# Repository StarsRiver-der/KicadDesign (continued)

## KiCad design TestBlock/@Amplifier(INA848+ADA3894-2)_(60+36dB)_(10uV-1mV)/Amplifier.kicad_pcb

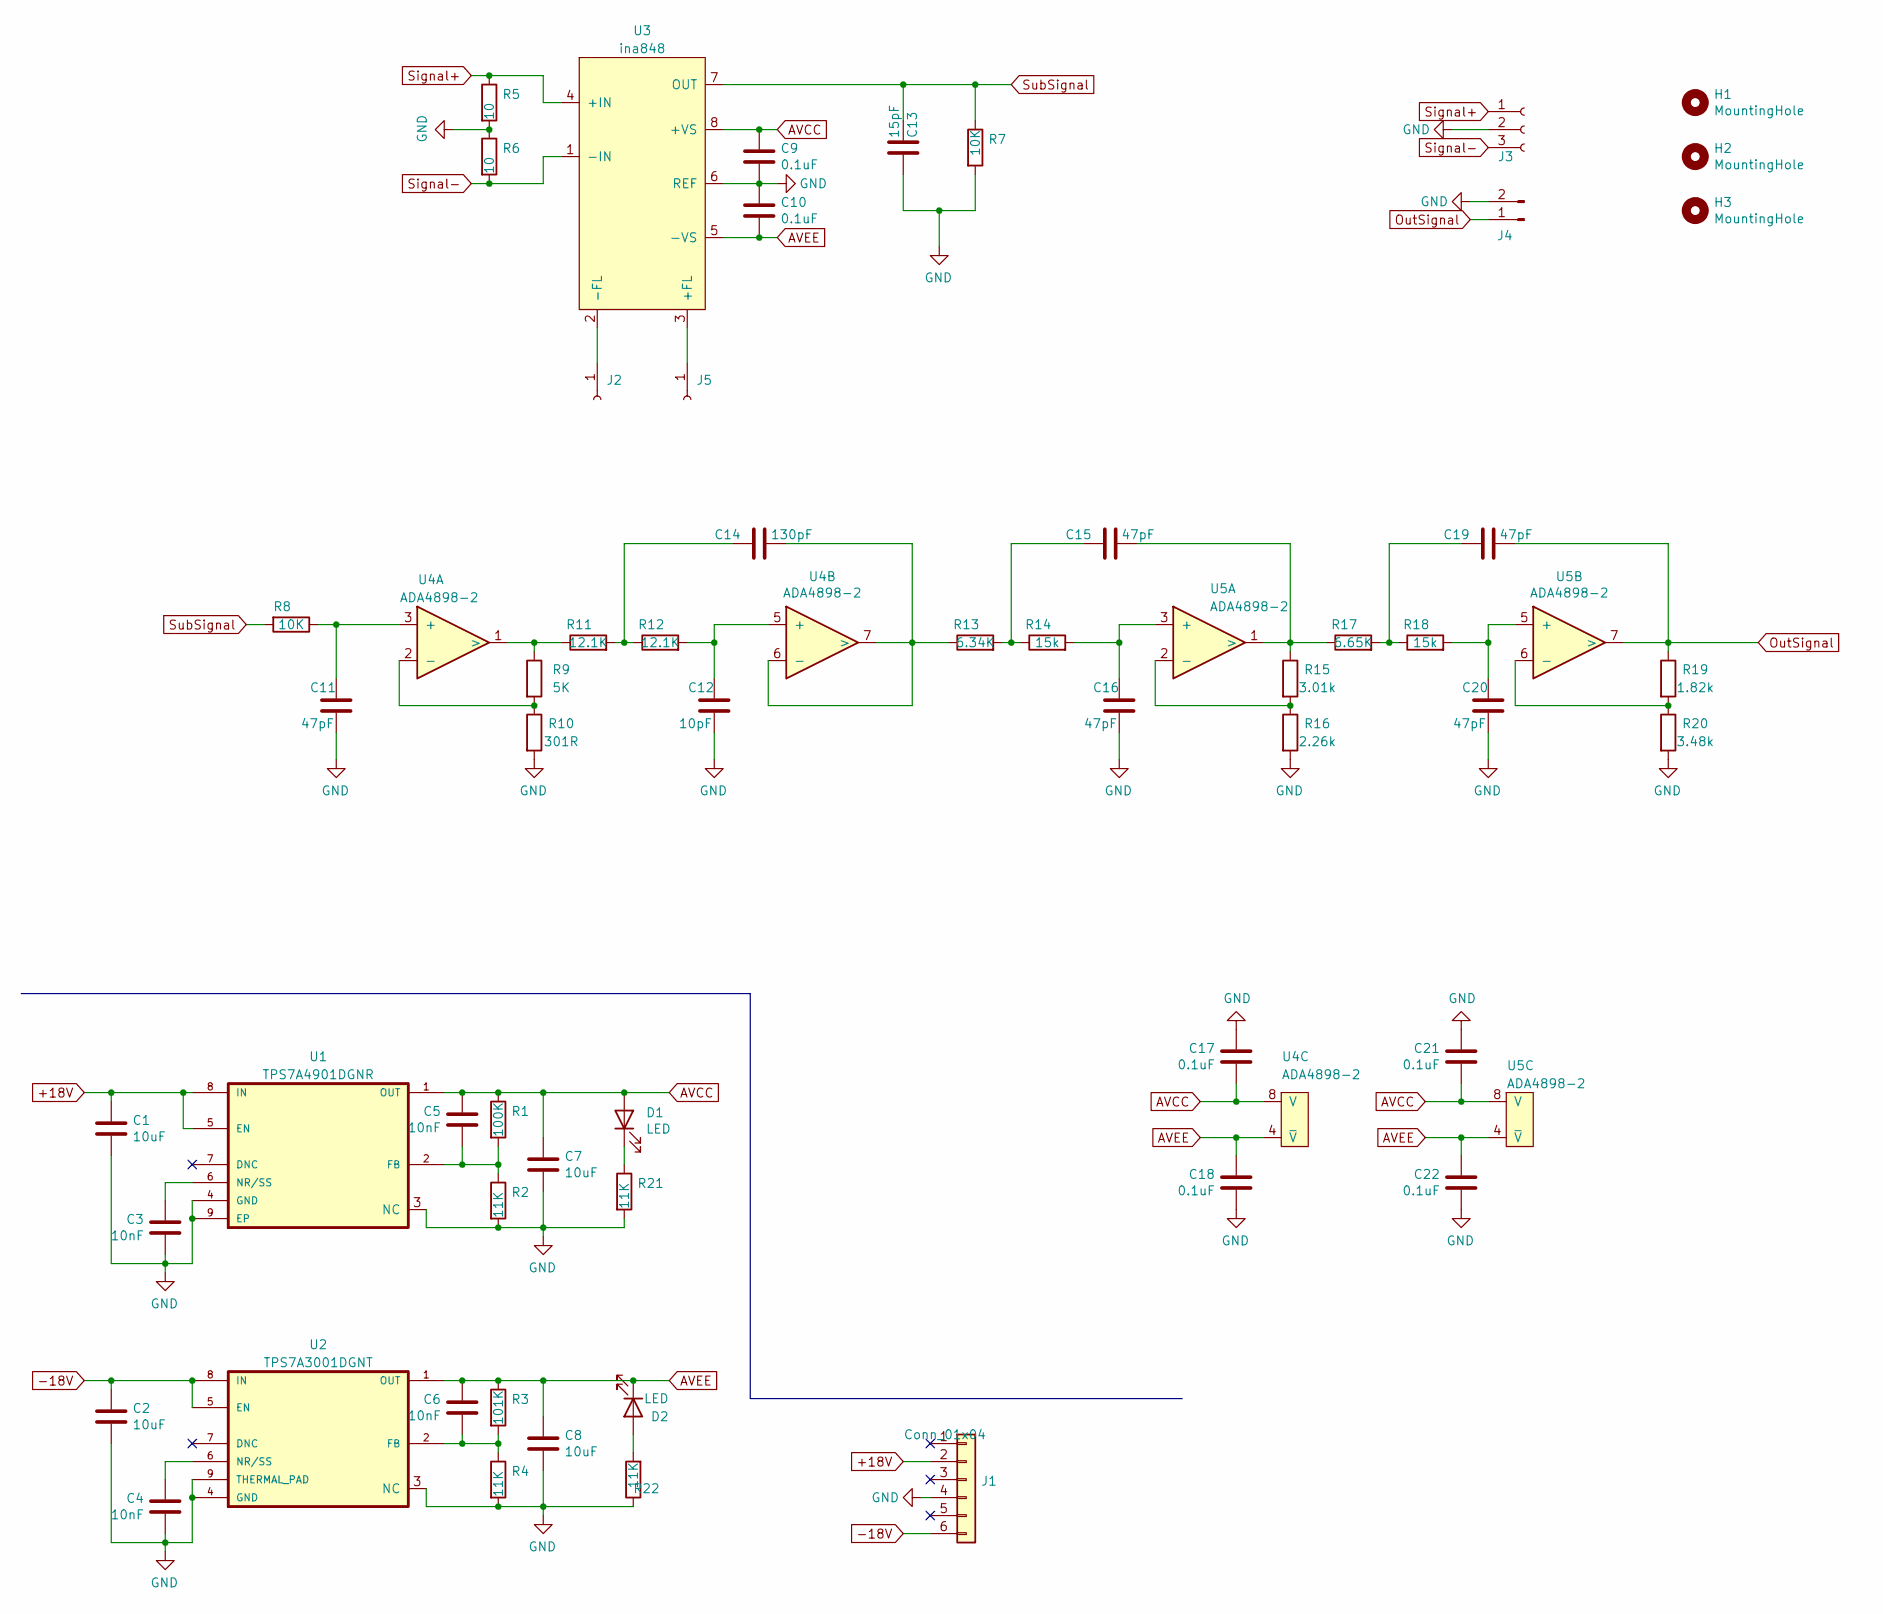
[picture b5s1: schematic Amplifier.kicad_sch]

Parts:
C1, C2, C7, C8: 10uF; C_0603_1608Metric
C3, C4, C5, C6: 10nF; C_0402_1005Metric
C9, C10, C17, C18, C21, C22: 0.1uF; C_1206_3216Metric
C11, C15, C16, C19, C20: 47pF; C_0402_1005Metric
C12: 10pF; C_0402_1005Metric
C13: 15pF; C_0402_1005Metric
C14: 130pF; C_0402_1005Metric
D1, D2: LED; LED_0402_1005Metric
H1, H2, H3: MountingHole; MountingHole_2.2mm_M2
J1: Conn_01x04; Multicomp_MC9A12-1034_2x03_P2.54mm_Vertical
J2, J5: Conn_01x01_Female; MountingPad_1mm
J3: Conn_01x03_Female; PinSocket_1x03_P2.54mm_Vertical
J4: Conn_01x02_Male; SMA_Amphenol_132134_Vertical
R1: 100K; R_0402_1005Metric
R2, R4, R21, R22: 11K; R_0402_1005Metric
R3: 101K; R_0402_1005Metric
R5, R6: 10; R_0402_1005Metric
R7, R8: 10K; R_0402_1005Metric
R9: 5K; R_0402_1005Metric
R10: 301R; R_0402_1005Metric
R11, R12: 12.1K; R_0402_1005Metric
R13: 6.34K; R_0402_1005Metric
R14, R18: 15k; R_0402_1005Metric
R15: 3.01k; R_0402_1005Metric
R16: 2.26k; R_0402_1005Metric
R17: 6.65K; R_0402_1005Metric
R19: 1.82k; R_0402_1005Metric
R20: 3.48k; R_0402_1005Metric
U1: TPS7A4901DGNR; SOP65P490X110-9N
U2: TPS7A3001DGNT; SOP65P490X110-9N
U3: ina848; SOIC-8_3.9x4.9mm_P1.27mm
U4, U5: ADA4898-2; SOIC-8-1EP_3.9x4.9mm_P1.27mm_EP2.29x3mm

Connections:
+18V: C1.1, J1.2, U1.5 (EN), U1.8 (IN)
-18V: C2.1, J1.6, U2.5 (EN), U2.8 (IN)
AVCC: C5.1, C7.1, C9.1, C17.2, C21.2, D1.2 (A), R1.1, U1.1 (OUT), U3.8 (+VS), U4.8 (V), U5.8 (V)
AVEE: C6.1, C8.1, C10.2, C18.1, C22.1, D2.1 (K), R3.1, U2.1 (OUT), U3.5 (-VS), U4.4 (~V), U5.4 (~V)
GND: C1.2, C2.2, C3.2, C4.2, C7.2, C8.2, C9.2, C10.1, C11.2, C12.2, C13.2, C16.2, C17.1, C18.2, C20.2, C21.1, C22.2, J1.4, J3.2, J4.2, R2.2, R4.2, R5.2, R6.1, R7.2, R10.2, R16.2, R20.2, R21.2, R22.1, U1.3 (NC), U1.4 (GND), U1.9 (EP), U2.3 (NC), U2.4 (GND), U2.9 (THERMAL_PAD), U3.6 (REF)
unnamed: C3.1, U1.6 (NR/SS)
unnamed: C4.1, U2.6 (NR/SS)
unnamed: C5.2, R1.2, R2.1, U1.2 (FB)
unnamed: C6.2, R3.2, R4.1, U2.2 (FB)
unnamed: C11.1, R8.1, U4.3 (+)
unnamed: C12.1, R12.2, U4.5 (+)
unnamed: C14.1, R11.2, R12.1
unnamed: C14.2, R13.1, U4.6 (-), U4.7 (>)
unnamed: C15.1, R13.2, R14.1
unnamed: C15.2, R15.1, R17.1, U5.1 (>)
unnamed: C16.1, R14.2, U5.3 (+)
unnamed: C19.1, R17.2, R18.1
unnamed: C20.1, R18.2, U5.5 (+)
unnamed: D1.1 (K), R21.1
unnamed: D2.2 (A), R22.2
unnamed: J2.1, U3.2 (-FL)
unnamed: J5.1, U3.3 (+FL)
unnamed: R9.2, R10.1, U4.2 (-)
unnamed: R9.1, R11.1, U4.1 (>)
unnamed: R15.2, R16.1, U5.2 (-)
unnamed: R19.2, R20.1, U5.6 (-)
OutSignal: C19.2, J4.1, R19.1, U5.7 (>)
Signal+: J3.1, R5.1, U3.4 (+IN)
Signal-: J3.3, R6.2, U3.1 (-IN)
SubSignal: C13.1, R7.1, R8.2, U3.7 (OUT)

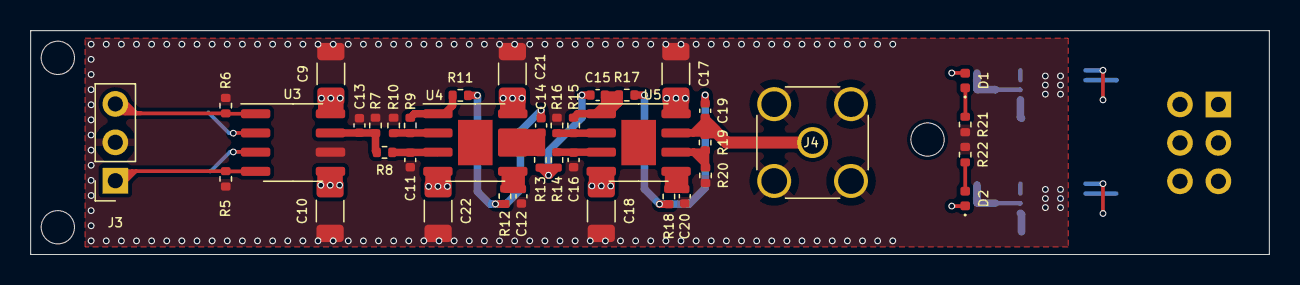
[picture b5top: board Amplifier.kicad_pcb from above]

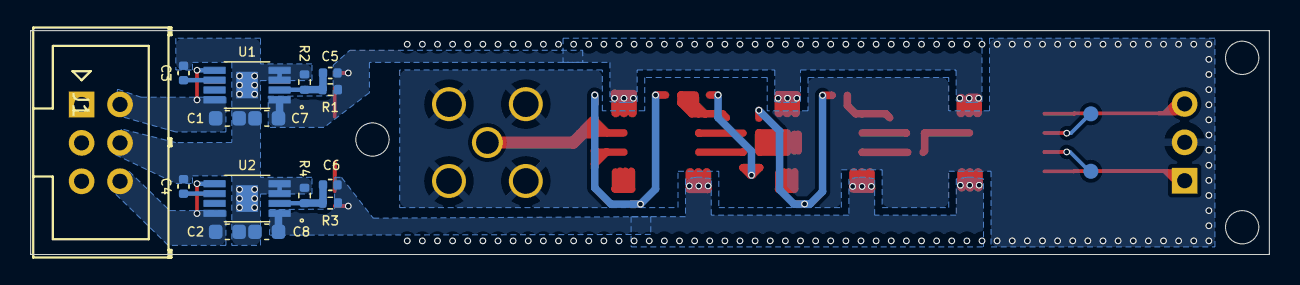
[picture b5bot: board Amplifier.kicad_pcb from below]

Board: 4 copper layers, 81.9 x 14.8 mm, 59 parts (17 on the bottom side), 30 nets.

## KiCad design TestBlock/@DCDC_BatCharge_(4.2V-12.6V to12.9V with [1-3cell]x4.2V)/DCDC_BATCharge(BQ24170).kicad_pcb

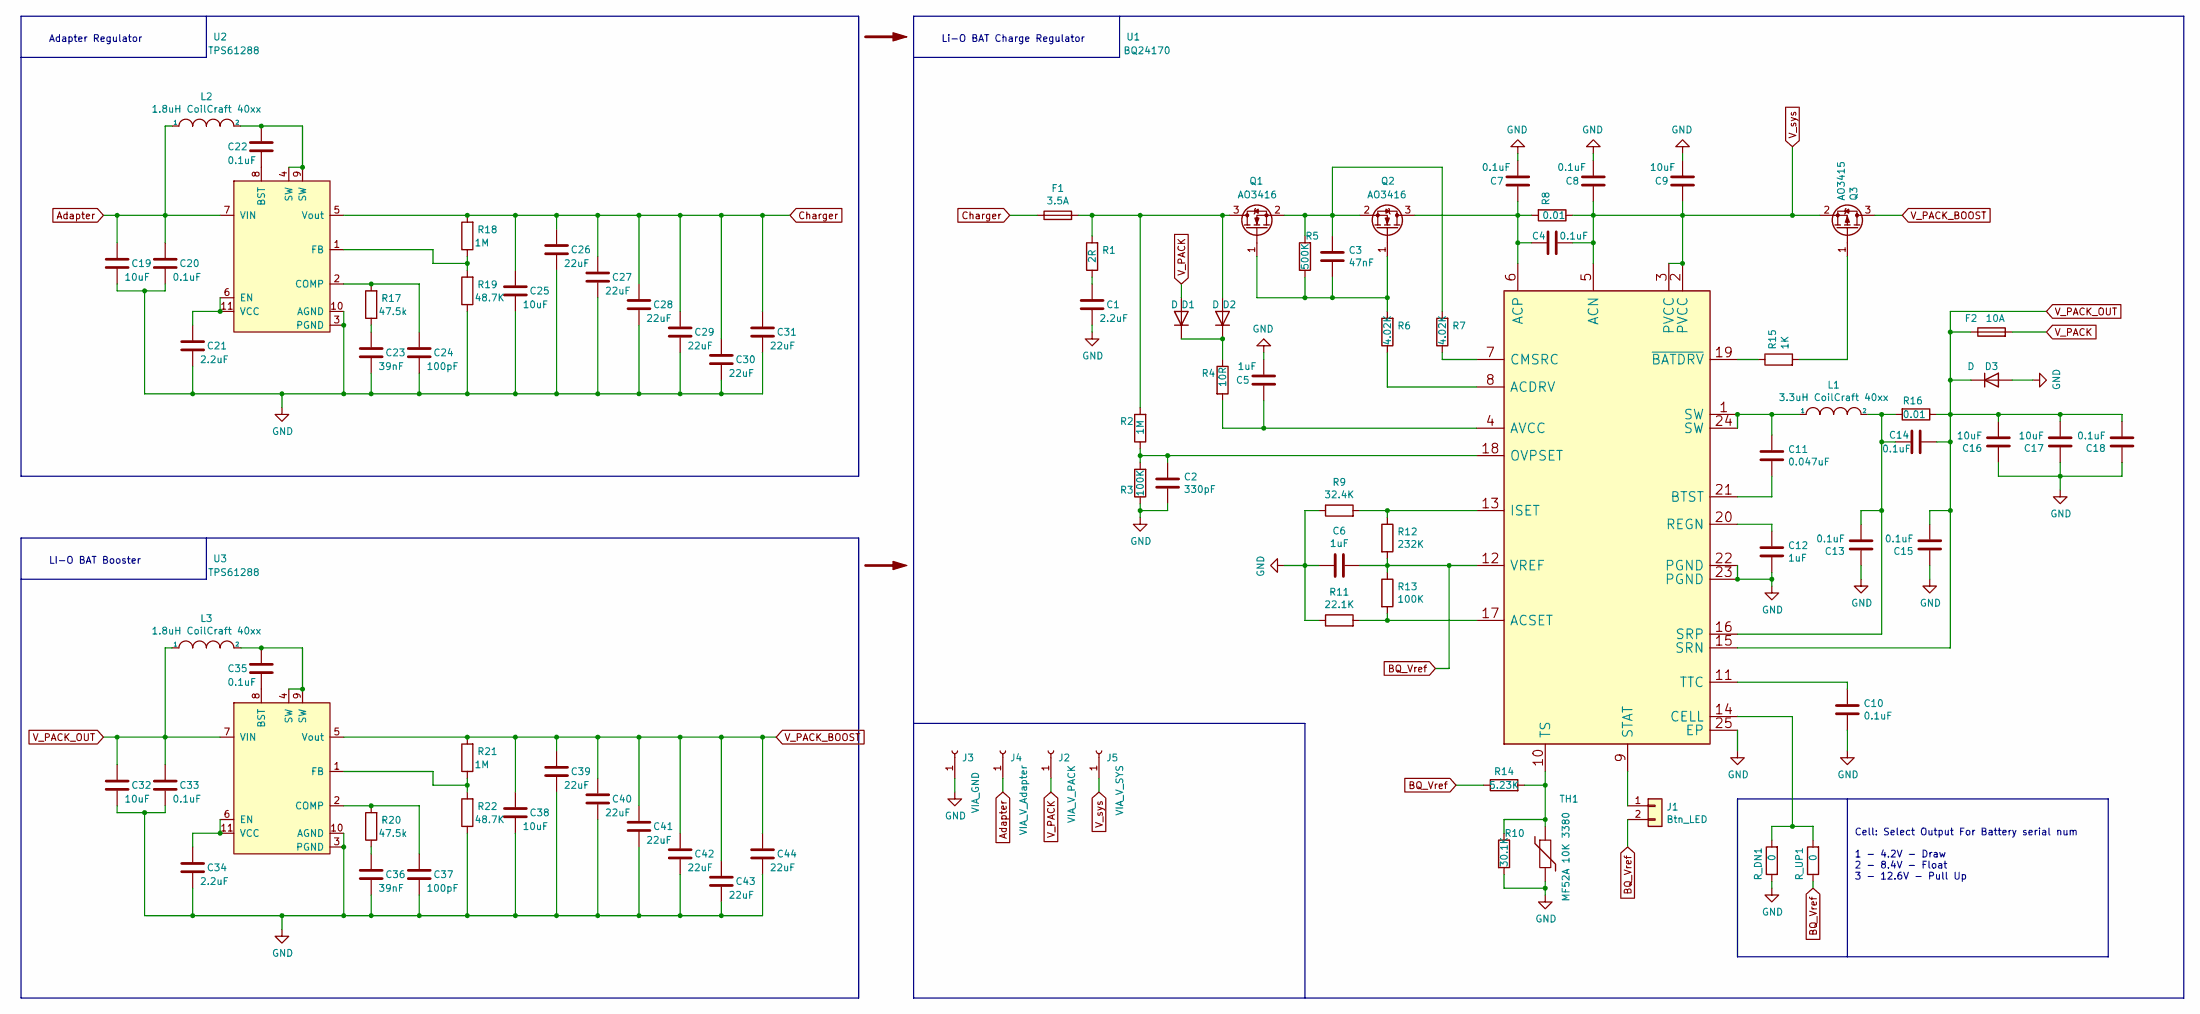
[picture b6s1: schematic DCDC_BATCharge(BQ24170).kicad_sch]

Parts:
C1, C21, C34: 2.2uF; C_0402_1005Metric
C2: 330pF; R_0402_1005Metric
C3: 47nF; C_0402_1005Metric
C4, C7, C8, C13, C14, C15, C20, C22, C33, C35: 0.1uF; C_0402_1005Metric
C5, C6, C12: 1uF; C_0603_1608Metric
C9, C16, C17: 10uF; C_0805_2012Metric
C10, C18: 0.1uF; C_0603_1608Metric
C11: 0.047uF; C_0402_1005Metric
C19, C25, C32, C38: 10uF; C_0603_1608Metric
C23, C36: 39nF; C_0402_1005Metric
C24, C37: 100pF; C_0402_1005Metric
C26, C27, C28, C29, C30, C31, C39, C40, C41, C42, C43, C44: 22uF; C_0805_2012Metric
D1, D2, D3: D; D_0603_1608Metric
F1: 3.5A; Fuse_0603_1608Metric
F2: 10A; Fuse_0603_1608Metric
J1: Btn_LED; PinHeader_1x02_P1.00mm_Vertical
J2: VIA_V_PACK; MountingHole_2.2mm_M2_Pad_Via
J3: VIA_GND; MountingHole_2.2mm_M2_Pad_Via
J4: VIA_V_Adapter; MountingHole_2.2mm_M2_Pad_Via
J5: VIA_V_SYS; MountingHole_2.2mm_M2_Pad_Via
L1: 3.3uH CoilCraft 40xx; L_Coilcraft_XxL4020
L2, L3: 1.8uH CoilCraft 40xx; L_Coilcraft_XxL4020
Q1, Q2: AO3416; SOT-23
Q3: AO3415; SOT-23
R1: 2R; R_0402_1005Metric
R2, R18, R21: 1M; R_0402_1005Metric
R3, R13: 100K; R_0402_1005Metric
R4: 10R; R_0402_1005Metric
R5: 500K; R_0402_1005Metric
R6, R7: 4.02K; R_0402_1005Metric
R8, R16: 0.01; R_0805_2012Metric
R9: 32.4K; R_0402_1005Metric
R10: 30.1K; R_0402_1005Metric
R11: 22.1K; R_0402_1005Metric
R12: 232K; R_0402_1005Metric
R14: 5.23K; R_0402_1005Metric
R15: 1K; R_0402_1005Metric
R17, R20: 47.5k; R_0402_1005Metric
R19, R22: 48.7K; R_0402_1005Metric
R_DN1: 0; R_0402_1005Metric
R_UP1: 0; R_0402_1005Metric
TH1: MF52A 10K 3380; R_Axial_DIN0204_L3.6mm_D1.6mm_P1.90mm_Vertical
U1: BQ24170; BQ24170RGYT
U2, U3: TPS61288

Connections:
Adapter: C19.2, C20.2, J4.1, L2.1, U2.7 (VIN)
BQ_Vref: C6.1, J1.2, R12.2, R13.1, R14.1, R_UP1.1, U1.12 (VREF)
Charger: C25.2, C26.2, C27.2, C28.2, C29.2, C30.2, C31.2, F1.1, R18.2, U2.5 (Vout)
GND: C1.1, C2.1, C5.1, C6.2, C7.1, C8.1, C9.1, C10.2, C12.2, C13.1, C15.1, C16.1, C17.1, C18.1, C19.1, C20.1, C21.1, C23.1, C24.1, C25.1, C26.1, C27.1, C28.1, C29.1, C30.1, C31.1, C32.1, C33.1, C34.1, C36.1, C37.1, C38.1, C39.1, C40.1, C41.1, C42.1, C43.1, C44.1, D3.2 (A), J3.1, R3.1, R9.1, R10.2, R11.1, R19.1, R22.1, R_DN1.1, TH1.2, U1.22 (PGND), U1.23 (PGND), U1.25 (EP), U2.3 (PGND), U2.10 (AGND), U3.3 (PGND), U3.10 (AGND)
unnamed: C1.2, R1.1
unnamed: C2.2, R2.1, R3.2, U1.18 (OVPSET)
unnamed: C3.1, Q1.1 (G), Q2.1 (G), R5.1, R6.2
unnamed: C3.2, Q1.2 (S), Q2.2 (S), R5.2, R7.2
unnamed: C4.1, C7.2, Q2.3 (D), R8.2, U1.6 (ACP)
unnamed: C5.2, R4.2, U1.4 (AVCC)
unnamed: C10.1, U1.11 (TTC)
unnamed: C11.1, L1.1, U1.1 (SW), U1.24 (SW)
unnamed: C11.2, U1.21 (BTST)
unnamed: C12.1, U1.20 (REGN)
unnamed: C13.2, C14.2, L1.2, R16.2, U1.16 (SRP)
unnamed: C21.2, U2.6 (EN), U2.11 (VCC)
unnamed: C22.1, U2.8 (BST)
unnamed: C22.2, L2.2, U2.4 (SW), U2.9 (SW)
unnamed: C23.2, R17.1
unnamed: C24.2, R17.2, U2.2 (COMP)
unnamed: C34.2, U3.6 (EN), U3.11 (VCC)
unnamed: C35.1, U3.8 (BST)
unnamed: C35.2, L3.2, U3.4 (SW), U3.9 (SW)
unnamed: C36.2, R20.1
unnamed: C37.2, R20.2, U3.2 (COMP)
unnamed: D1.1 (K), D2.1 (K), R4.1
unnamed: D2.2 (A), F1.2, Q1.3 (D), R1.2, R2.2
unnamed: J1.1, U1.9 (STAT)
unnamed: Q3.1 (G), R15.2
unnamed: R6.1, U1.8 (ACDRV)
unnamed: R7.1, U1.7 (CMSRC)
unnamed: R10.1, R14.2, TH1.1, U1.10 (TS)
unnamed: R11.2, R13.2, U1.17 (ACSET)
unnamed: R9.2, R12.1, U1.13 (ISET)
unnamed: R15.1, U1.19 (~BATDRV)
unnamed: R18.1, R19.2, U2.1 (FB)
unnamed: R21.1, R22.2, U3.1 (FB)
unnamed: R_DN1.2, R_UP1.2, U1.14 (CELL)
V_PACK: D1.2 (A), F2.2, J2.1
V_PACK_BOOST: C38.2, C39.2, C40.2, C41.2, C42.2, C43.2, C44.2, Q3.3 (D), R21.2, U3.5 (Vout)
V_PACK_OUT: C14.1, C15.2, C16.2, C17.2, C18.2, C32.2, C33.2, D3.1 (K), F2.1, L3.1, R16.1, U1.15 (SRN), U3.7 (VIN)
V_sys: C4.2, C8.2, C9.2, J5.1, Q3.2 (S), R8.1, U1.2 (PVCC), U1.3 (PVCC), U1.5 (ACN)

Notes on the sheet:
Cell: Select Output For Battery serial num 1 - 4.2V - Draw 2 - 8.4V - Float 3 - 12.6V - Pull Up
Adapter Regulator
LI-O BAT Booster
Li-O BAT Charge Regulator

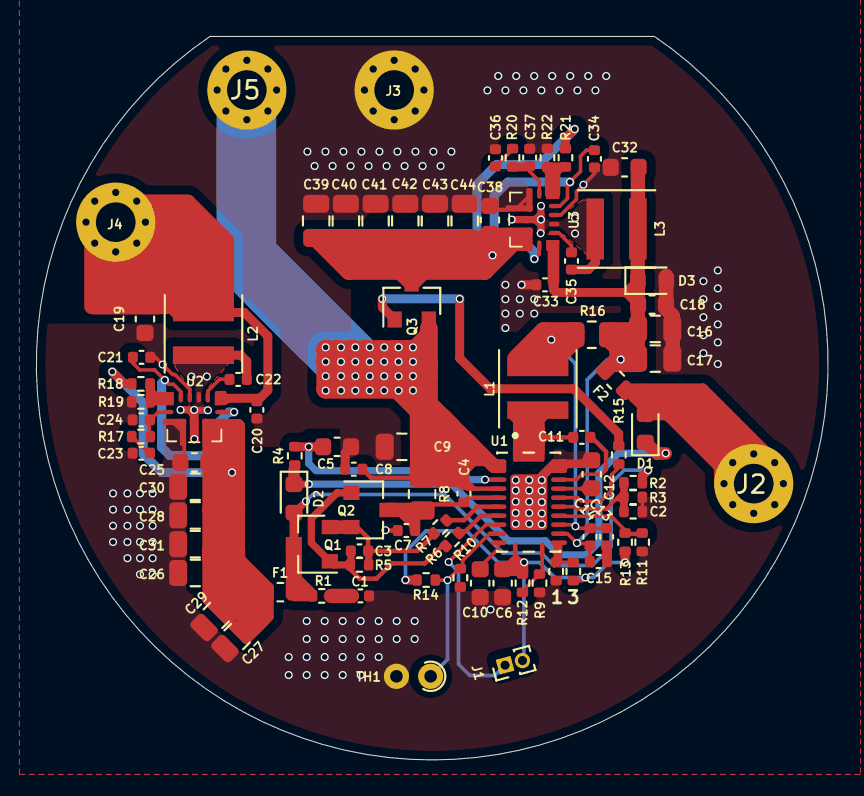
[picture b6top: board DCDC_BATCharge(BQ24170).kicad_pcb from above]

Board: 2 copper layers, 44.0 x 40.2 mm, 88 parts (0 on the bottom side), 42 nets.

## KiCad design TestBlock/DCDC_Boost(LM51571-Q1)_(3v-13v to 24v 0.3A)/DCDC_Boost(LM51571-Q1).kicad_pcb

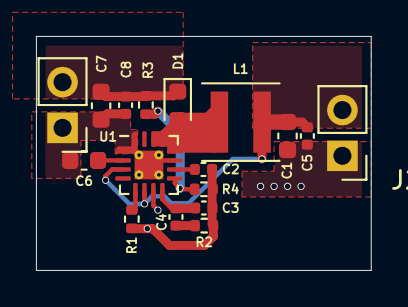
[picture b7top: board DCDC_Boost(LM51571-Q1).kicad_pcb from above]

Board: 2 copper layers, 18.6 x 13.0 mm, 17 parts (0 on the bottom side), 10 nets.

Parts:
C1, C7: 4.7uF; C_0603_1608Metric
C2: 68nF; C_0402_1005Metric
C3: 300pF; C_0402_1005Metric
C4: 27nF; C_0402_1005Metric
C5, C8: 100nF; C_0402_1005Metric
C6: 1uF; C_0603_1608Metric
D1: 0.55V 1A; D_0603_1608Metric
J1, J2: Conn_01x02; PinHeader_1x02_P2.54mm_Vertical
L1: 8.2uH; L_Coilcraft_XxL4020
R1: 24.9K; R_0402_1005Metric
R2: 1.18K; R_0402_1005Metric
R3: 57.6K; R_0402_1005Metric
R4: 2.49K; R_0402_1005Metric
U1: LM51571; WQFN-16-1EP_3x3mm_P0.5mm_EP1.6x1.6mm_ThermalVias

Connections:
BAT: C1.1, C5.2, J2.2, L1.1, U1.3, U1.6
GND: C1.2, C2.2, C3.2, C5.1, C6.1, C7.2, C8.2, J1.1, J2.1, R1.2, R2.2, R4.2, U1.1, U1.7, U1.11, U1.16, U1.17
unnamed: C2.1, U1.10
unnamed: C3.1, C4.1, U1.8
unnamed: C4.2, R2.1
unnamed: C6.2, U1.2
unnamed: D1.2, L1.2, U1.12, U1.13, U1.14
unnamed: R1.1, U1.5
unnamed: R3.2, R4.1, U1.9
V24: C7.1, C8.1, D1.1, J1.2, R3.1
